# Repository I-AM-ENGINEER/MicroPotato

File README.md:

# MicroPotato
Old allwinner v3s devboard created just for fun

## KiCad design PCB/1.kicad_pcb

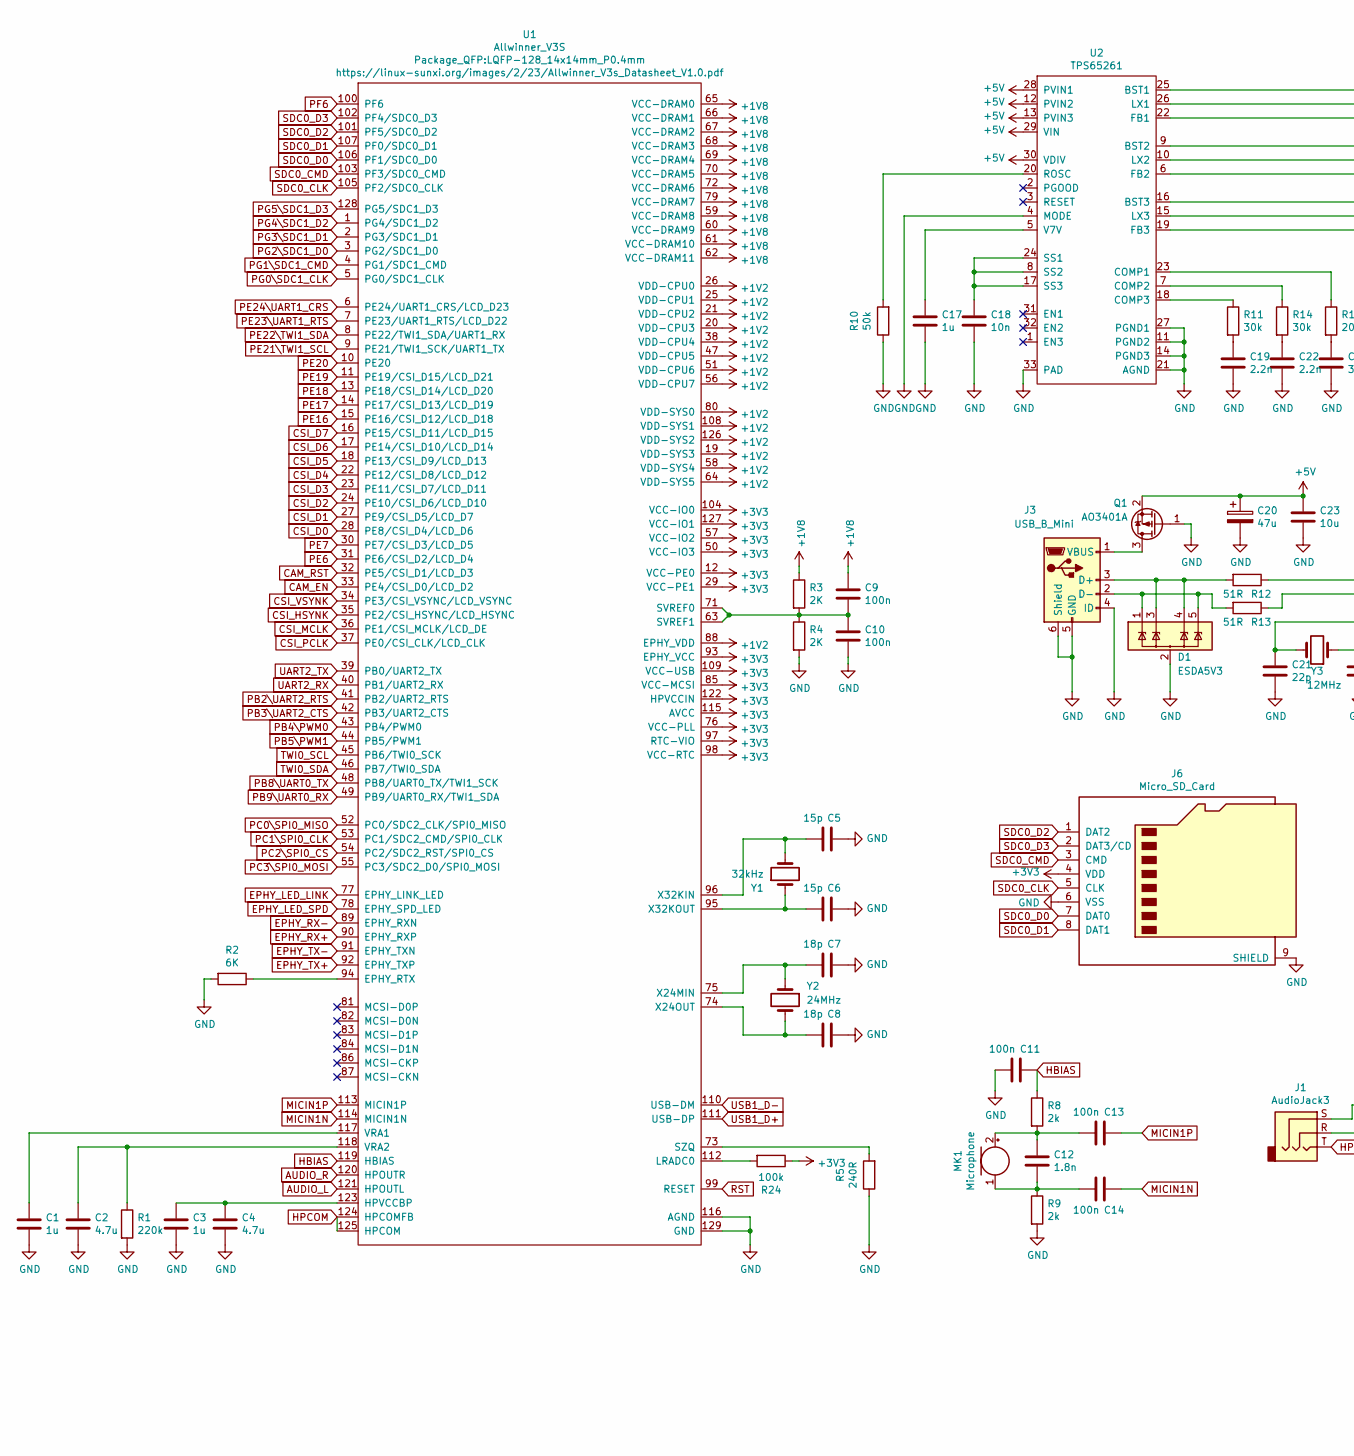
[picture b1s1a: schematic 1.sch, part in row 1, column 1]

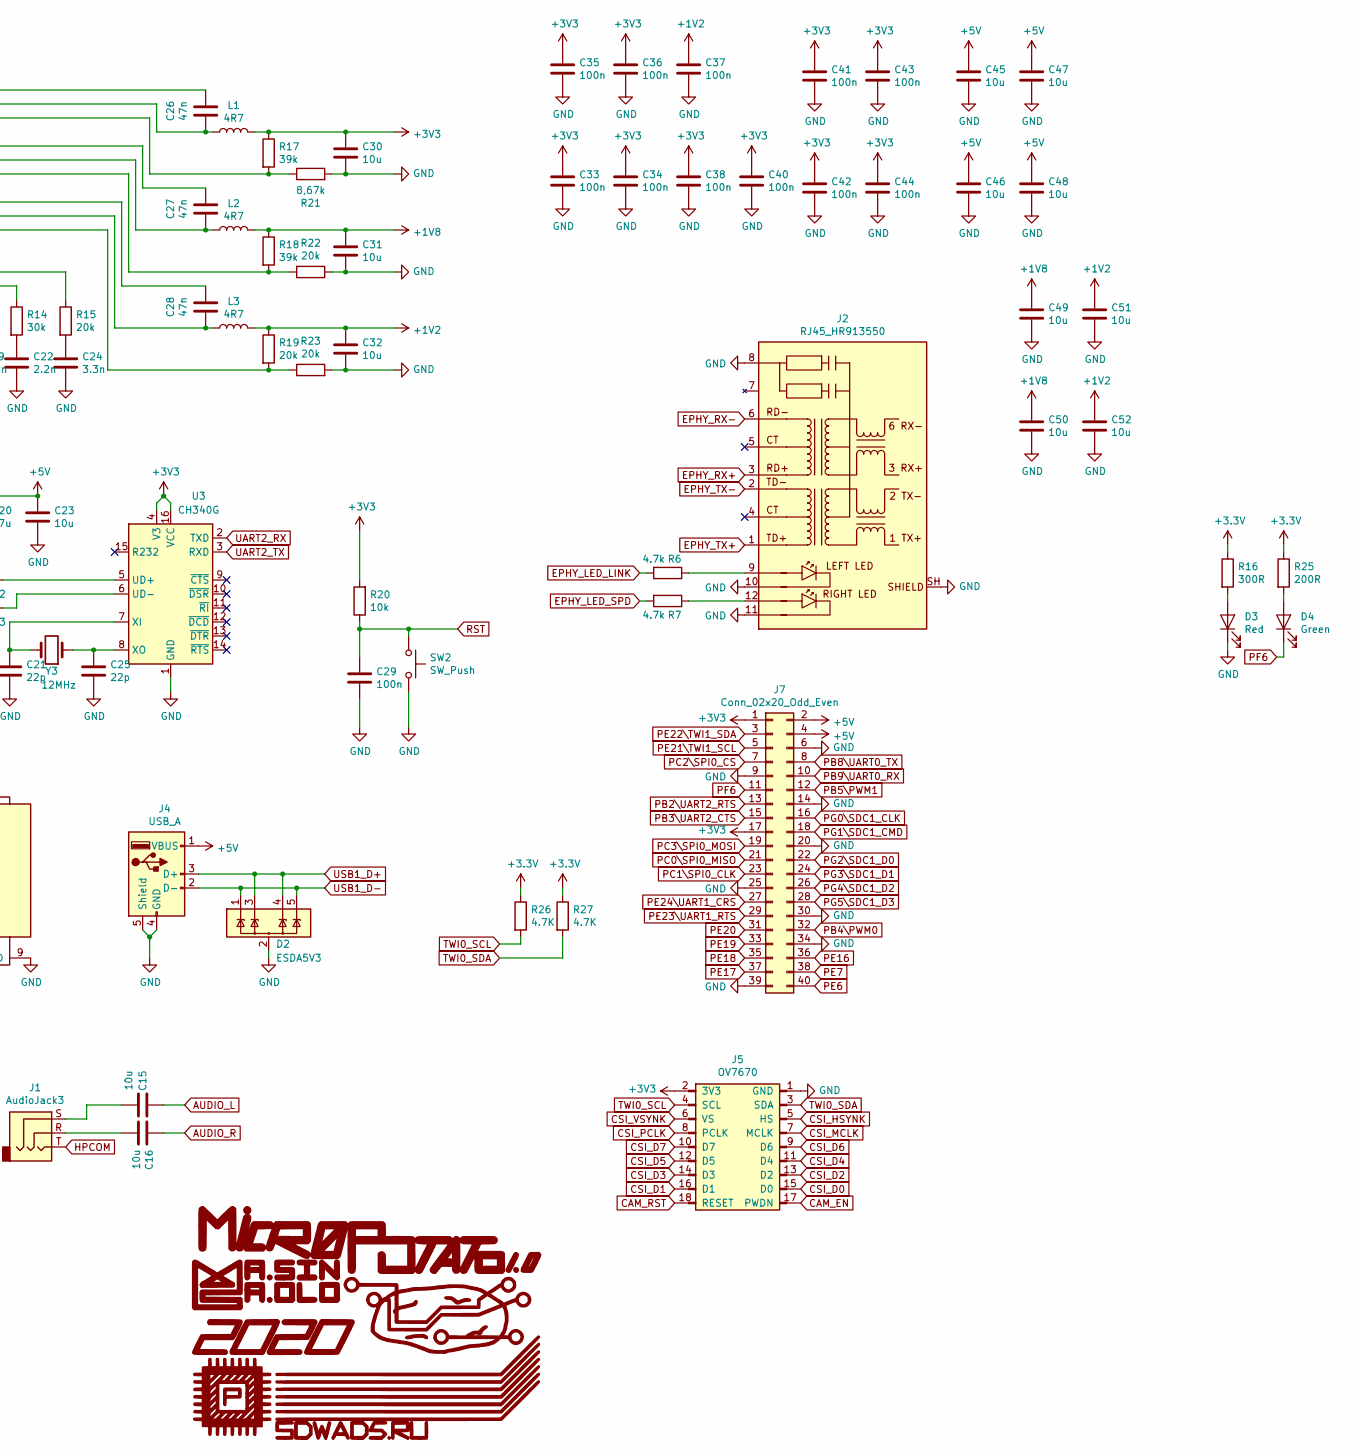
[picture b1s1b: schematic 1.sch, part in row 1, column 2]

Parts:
C1, C3, C17: 1u; C_0603_1608Metric
C2, C4: 4.7u; C_0603_1608Metric
C5, C6: 15p; C_0603_1608Metric
C7, C8: 18p; C_0603_1608Metric
C9, C10, C11, C13, C14, C29, C33, C34, C35, C36, C37, C38, C40, C41, C42, C43: 100n; C_0603_1608Metric
C12: 1.8n; C_0603_1608Metric
C15, C16, C23, C30, C31, C32, C45, C46, C47, C49, C51: 10u; C_0603_1608Metric
C18: 10n; C_0603_1608Metric
C19, C22: 2.2n; C_0603_1608Metric
C20: 47u; CP_Elec_6.3x5.7
C21, C25: 22p; C_0603_1608Metric
C24: 3.3n; C_0603_1608Metric
C26, C27, C28: 47n; C_0603_1608Metric
C44: 100n; C_0603_1608Metric_Pad1.05x0.95mm_HandSolder
C48, C50, C52: 10u; C_0603_1608Metric_Pad1.05x0.95mm_HandSolder
D1, D2: ESDA5V3; SOT-23-5
D3: Red; LED_0603_1608Metric
D4: Green; LED_0603_1608Metric
J1: AudioJack3; Jack_3.5mm_Switronic_ST-005-G_horizontal
J2: RJ45_HR913550; RJ45_Hanrun_HR911105A
J3: USB_B_Mini; USB_Mini-B_Lumberg_2486_01_Horizontal
J4: USB_A; USB_A_C42421
J5: OV7670; PinSocket_2x09_P2.54mm_Vertical
J6: Micro_SD_Card; microSD_TF115K
J7: Conn_02x20_Odd_Even; PinHeader_2x20_P2.54mm_Vertical
L1, L2, L3: 4R7; L_Bourns-SRN4018
MK1: Microphone; MIC_10mm
Q1: AO3401A; SOT-23
R1: 220k; R_0603_1608Metric
R2: 6K; R_0603_1608Metric
R3, R4: 2K; R_0603_1608Metric
R5: 240R; R_0603_1608Metric
R6, R7: 4.7k; R_0603_1608Metric
R8, R9: 2k; R_0603_1608Metric
R10: 50k; R_0603_1608Metric
R11, R14: 30k; R_0603_1608Metric
R12, R13: 51R; R_0603_1608Metric
R15, R19, R22, R23: 20k; R_0603_1608Metric
R16: 300R; R_0603_1608Metric
R17, R18: 39k; R_0603_1608Metric
R20: 10k; R_0603_1608Metric
R21: 8,67k; R_0603_1608Metric
R24: 100k; R_0603_1608Metric
R25: 200R; R_0603_1608Metric
R26, R27: 4.7K; R_0603_1608Metric
SW2: SW_Push; SW_SPST_B3SL-1022P
U1: Allwinner_V3S; LQFP-128_14x14mm_P0.4mm
U2: TPS65261; QFN-32-1EP_5x5mm_P0.5mm_EP3.45x3.45mm
U3: CH340G; SOIC-16_3.9x9.9mm_P1.27mm
Y1: 32kHz; Crystal_C38-LF_D3.0mm_L8.0mm_Horizontal_1EP_style1
Y2: 24MHz; Crystal_SMD_5032-2Pin_5.0x3.2mm_HandSoldering
Y3: 12MHz; Crystal_SMD_5032-2Pin_5.0x3.2mm_HandSoldering

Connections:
+1V2: C32.1, C37.1, C51.1, C52.1, L3.2, R19.1, U1.19 (VDD-SYS3), U1.20 (VDD-CPU3), U1.21 (VDD-CPU2), U1.25 (VDD-CPU1), U1.26 (VDD-CPU0), U1.38 (VDD-CPU4), U1.47 (VDD-CPU5), U1.51 (VDD-CPU6), U1.56 (VDD-CPU7), U1.58 (VDD-SYS4), U1.64 (VDD-SYS5), U1.80 (VDD-SYS0), U1.88 (EPHY_VDD), U1.108 (VDD-SYS1), U1.126 (VDD-SYS2)
+1V8: C9.1, C31.1, C49.1, C50.1, L2.2, R3.1, R18.1, U1.59 (VCC-DRAM8), U1.60 (VCC-DRAM9), U1.61 (VCC-DRAM10), U1.62 (VCC-DRAM11), U1.65 (VCC-DRAM0), U1.66 (VCC-DRAM1), U1.67 (VCC-DRAM2), U1.68 (VCC-DRAM3), U1.69 (VCC-DRAM4), U1.70 (VCC-DRAM5), U1.72 (VCC-DRAM6), U1.79 (VCC-DRAM7)
+5V: C20.1, C23.1, C45.1, C46.1, C47.1, C48.1, J4.1 (VBUS), J7.2, J7.4, Q1.2 (S), U2.12 (PVIN2), U2.13 (PVIN3), U2.28 (PVIN1), U2.29 (VIN), U2.30 (VDIV)
AUDIO_L: C15.1, U1.121 (HPOUTL)
AUDIO_R: C16.1, U1.120 (HPOUTR)
CAM_EN: J5.17 (PWDN), U1.33 (PE4/CSI_D0/LCD_D2)
CAM_RST: J5.18 (RESET), U1.32 (PE5/CSI_D1/LCD_D3)
CSI_D0: J5.15 (D0), U1.28 (PE8/CSI_D4/LCD_D6)
CSI_D1: J5.16 (D1), U1.27 (PE9/CSI_D5/LCD_D7)
CSI_D2: J5.13 (D2), U1.24 (PE10/CSI_D6/LCD_D10)
CSI_D3: J5.14 (D3), U1.23 (PE11/CSI_D7/LCD_D11)
CSI_D4: J5.11 (D4), U1.22 (PE12/CSI_D8/LCD_D12)
CSI_D5: J5.12 (D5), U1.18 (PE13/CSI_D9/LCD_D13)
CSI_D6: J5.9 (D6), U1.17 (PE14/CSI_D10/LCD_D14)
CSI_D7: J5.10 (D7), U1.16 (PE15/CSI_D11/LCD_D15)
CSI_HSYNK: J5.5 (HS), U1.35 (PE2/CSI_HSYNC/LCD_HSYNC)
CSI_MCLK: J5.7 (MCLK), U1.36 (PE1/CSI_MCLK/LCD_DE)
CSI_PCLK: J5.8 (PCLK), U1.37 (PE0/CSI_CLK/LCD_CLK)
CSI_VSYNK: J5.6 (VS), U1.34 (PE3/CSI_VSYNC/LCD_VSYNC)
EPHY_LED_LINK: R6.2, U1.77 (EPHY_LINK_LED)
EPHY_LED_SPD: R7.2, U1.78 (EPHY_SPD_LED)
EPHY_RX+: J2.3 (RD+), U1.90 (EPHY_RXP)
EPHY_RX-: J2.6 (RD-), U1.89 (EPHY_RXN)
EPHY_TX+: J2.1 (TD+), U1.92 (EPHY_TXP)
EPHY_TX-: J2.2 (TD-), U1.91 (EPHY_TXN)
GND: C1.2, C2.2, C3.2, C4.2, C5.1, C6.1, C7.1, C8.1, C10.2, C11.2, C17.2, C18.2, C19.2, C20.2, C21.1, C22.2, C23.2, C24.2, C25.2, C29.2, C30.2, C31.2, C32.2, C33.2, C34.2, C35.2, C36.2, C37.2, C38.2, C40.2, C41.2, C42.2, C43.2, C44.2, C45.2, C46.2, C47.2, C48.2, C49.2, C50.2, C51.2, C52.2, D1.2 (GND), D2.2 (GND), D3.1 (K), J2.8, J2.10 (LLED-), J2.11 (RLED-), J2.SH (SHIELD), J3.4 (ID), J3.5 (GND), J3.6 (Shield), J4.4 (GND), J4.5 (Shield), J5.1 (GND), J6.6 (VSS), J6.9 (SHIELD), J7.6, J7.9, J7.14, J7.20, J7.25, J7.30, J7.34, J7.39, Q1.1 (G), R1.2, R2.2, R4.2, R5.1, R9.2, R10.1, R21.2, R22.1, R23.2, SW2.2, U1.116 (AGND), U1.129 (GND), U2.4 (MODE), U2.11 (PGND2), U2.14 (PGND3), U2.21 (AGND), U2.27 (PGND1), U2.33 (PAD), U3.1 (GND)
HBIAS: C11.1, R8.1, U1.119 (HBIAS)
HPCOM: J1.T, U1.124 (HPCOMFB), U1.125 (HPCOM)
MICIN1N: C14.1, U1.114 (MICIN1N)
MICIN1P: C13.1, U1.113 (MICIN1P)
unnamed: C1.1, U1.117 (VRA1)
unnamed: C2.1, R1.1, U1.118 (VRA2)
unnamed: C3.1, C4.1, U1.123 (HPVCCBP)
unnamed: C5.2, U1.96 (X32KIN), Y1.2
unnamed: C6.2, U1.95 (X32KOUT), Y1.1
unnamed: C7.2, U1.75 (X24MIN), Y2.1
unnamed: C8.2, U1.74 (X24OUT), Y2.2
unnamed: C9.2, C10.1, R3.2, R4.1, U1.63 (SVREF1), U1.71 (SVREF0)
unnamed: C12.1, C13.2, MK1.2 (+), R8.2
unnamed: C12.2, C14.2, MK1.1 (-), R9.1
unnamed: C15.2, J1.S
unnamed: C16.2, J1.R
unnamed: C17.1, U2.5 (V7V)
unnamed: C18.1, U2.8 (SS2), U2.17 (SS3), U2.24 (SS1)
unnamed: C19.1, R11.2
unnamed: C21.2, U3.7 (XI), Y3.2
unnamed: C22.1, R14.2
unnamed: C24.1, R15.2
unnamed: C25.1, U3.8 (XO), Y3.1
unnamed: C26.1, U2.25 (BST1)
unnamed: C26.2, L1.1, U2.26 (LX1)
unnamed: C27.1, U2.9 (BST2)
unnamed: C27.2, L2.1, U2.10 (LX2)
unnamed: C28.1, U2.16 (BST3)
unnamed: C28.2, L3.1, U2.15 (LX3)
unnamed: D1.1 (IO1), D1.5 (IO5), J3.2 (D-), R13.2
unnamed: D1.3 (IO2), D1.4 (IO4), J3.3 (D+), R12.2
unnamed: D3.2 (A), R16.2
unnamed: D4.2 (A), R25.2
unnamed: J2.9 (LLED+), R6.1
unnamed: J2.12 (RLED+), R7.1
unnamed: J3.1 (VBUS), Q1.3 (D)
unnamed: R2.1, U1.94 (EPHY_RTX)
unnamed: R5.2, U1.73 (SZQ)
unnamed: R10.2, U2.20 (ROSC)
unnamed: R11.1, U2.18 (COMP3)
unnamed: R12.1, U3.5 (UD+)
unnamed: R13.1, U3.6 (UD-)
unnamed: R14.1, U2.7 (COMP2)
unnamed: R15.1, U2.23 (COMP1)
unnamed: R17.2, R21.1, U2.22 (FB1)
unnamed: R18.2, R22.2, U2.6 (FB2)
unnamed: R19.2, R23.1, U2.19 (FB3)
unnamed: R24.2, U1.112 (LRADC0)
PB2\UART2_RTS: J7.13, U1.41 (PB2/UART2_RTS)
PB3\UART2_CTS: J7.15, U1.42 (PB3/UART2_CTS)
PB4\PWM0: J7.32, U1.43 (PB4/PWM0)
PB5\PWM1: J7.12, U1.44 (PB5/PWM1)
PB8\UART0_TX: J7.8, U1.48 (PB8/UART0_TX/TWI1_SCK)
PB9\UART0_RX: J7.10, U1.49 (PB9/UART0_RX/TWI1_SDA)
PC0\SPI0_MISO: J7.21, U1.52 (PC0/SDC2_CLK/SPI0_MISO)
PC1\SPI0_CLK: J7.23, U1.53 (PC1/SDC2_CMD/SPI0_CLK)
PC2\SPI0_CS: J7.7, U1.54 (PC2/SDC2_RST/SPI0_CS)
PC3\SPI0_MOSI: J7.19, U1.55 (PC3/SDC2_D0/SPI0_MOSI)
PE6: J7.40, U1.31 (PE6/CSI_D2/LCD_D4)
PE7: J7.38, U1.30 (PE7/CSI_D3/LCD_D5)
PE16: J7.36, U1.15 (PE16/CSI_D12/LCD_D18)
PE17: J7.37, U1.14 (PE17/CSI_D13/LCD_D19)
PE18: J7.35, U1.13 (PE18/CSI_D14/LCD_D20)
PE19: J7.33, U1.11 (PE19/CSI_D15/LCD_D21)
PE20: J7.31, U1.10 (PE20)
PE21\TWI1_SCL: J7.5, U1.9 (PE21/TWI1_SCK/UART1_TX)
PE22\TWI1_SDA: J7.3, U1.8 (PE22/TWI1_SDA/UART1_RX)
PE23\UART1_RTS: J7.29, U1.7 (PE23/UART1_RTS/LCD_D22)
PE24\UART1_CRS: J7.27, U1.6 (PE24/UART1_CRS/LCD_D23)
PF6: D4.1 (K), J7.11, U1.100 (PF6)
PG0\SDC1_CLK: J7.16, U1.5 (PG0/SDC1_CLK)
PG1\SDC1_CMD: J7.18, U1.4 (PG1/SDC1_CMD)
PG2\SDC1_D0: J7.22, U1.3 (PG2/SDC1_D0)
PG3\SDC1_D1: J7.24, U1.2 (PG3/SDC1_D1)
PG4\SDC1_D2: J7.26, U1.1 (PG4/SDC1_D2)
PG5\SDC1_D3: J7.28, U1.128 (PG5/SDC1_D3)
RST: C29.1, R20.1, SW2.1, U1.99 (RESET)
SDC0_CLK: J6.5 (CLK), U1.105 (PF2/SDC0_CLK)
SDC0_CMD: J6.3 (CMD), U1.103 (PF3/SDC0_CMD)
SDC0_D0: J6.7 (DAT0), U1.106 (PF1/SDC0_D0)
SDC0_D1: J6.8 (DAT1), U1.107 (PF0/SDC0_D1)
SDC0_D2: J6.1 (DAT2), U1.101 (PF5/SDC0_D2)
SDC0_D3: J6.2 (DAT3/CD), U1.102 (PF4/SDC0_D3)
TWI0_SCL: J5.4 (SCL), R26.2, U1.45 (PB6/TWI0_SCK)
TWI0_SDA: J5.3 (SDA), R27.2, U1.46 (PB7/TWI0_SDA)
UART2_RX: U1.40 (PB1/UART2_RX), U3.2 (TXD)
UART2_TX: U1.39 (PB0/UART2_TX), U3.3 (RXD)
USB1_D+: D2.3 (IO2), D2.4 (IO4), J4.3 (D+), U1.111 (USB-DP)
USB1_D-: D2.1 (IO1), D2.5 (IO5), J4.2 (D-), U1.110 (USB-DM)

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
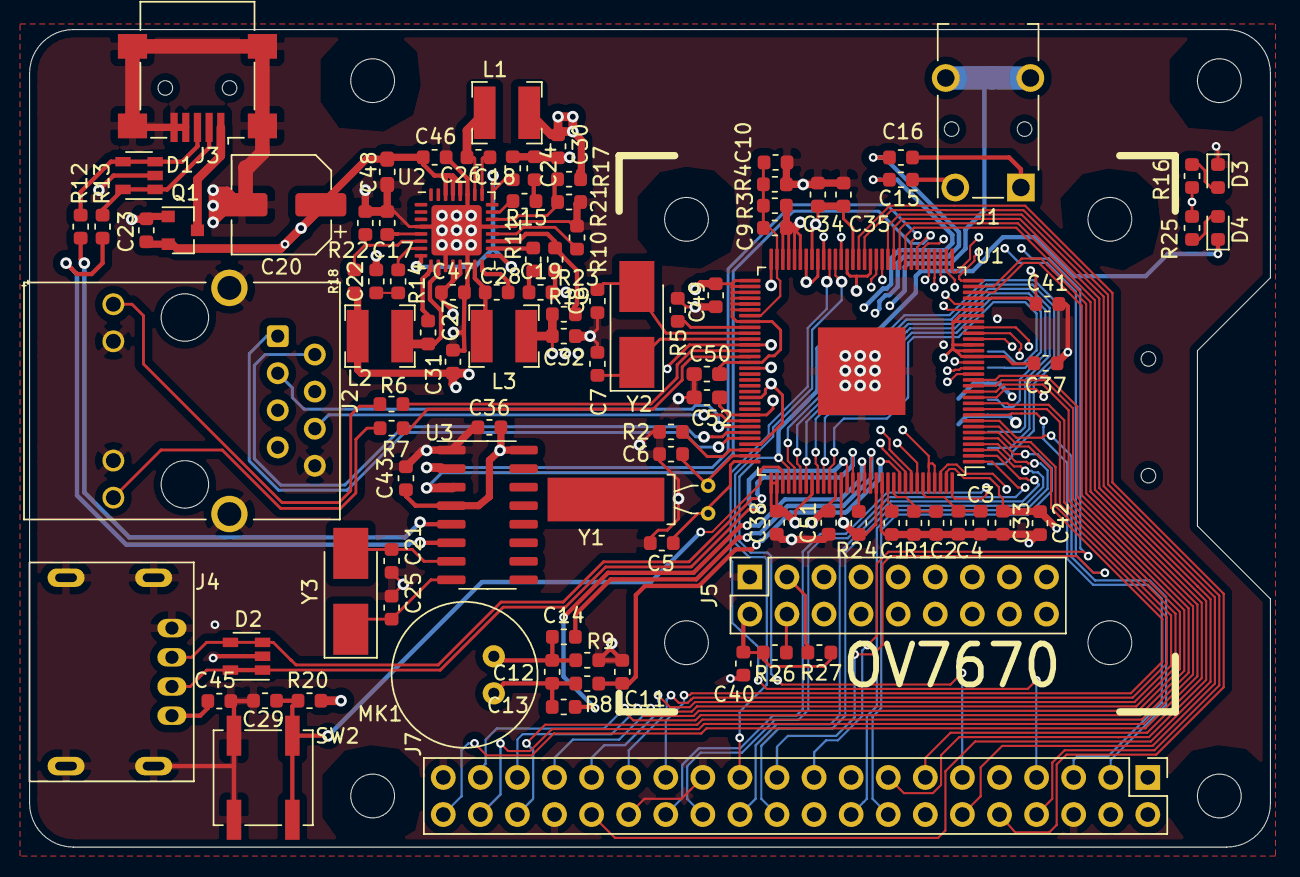
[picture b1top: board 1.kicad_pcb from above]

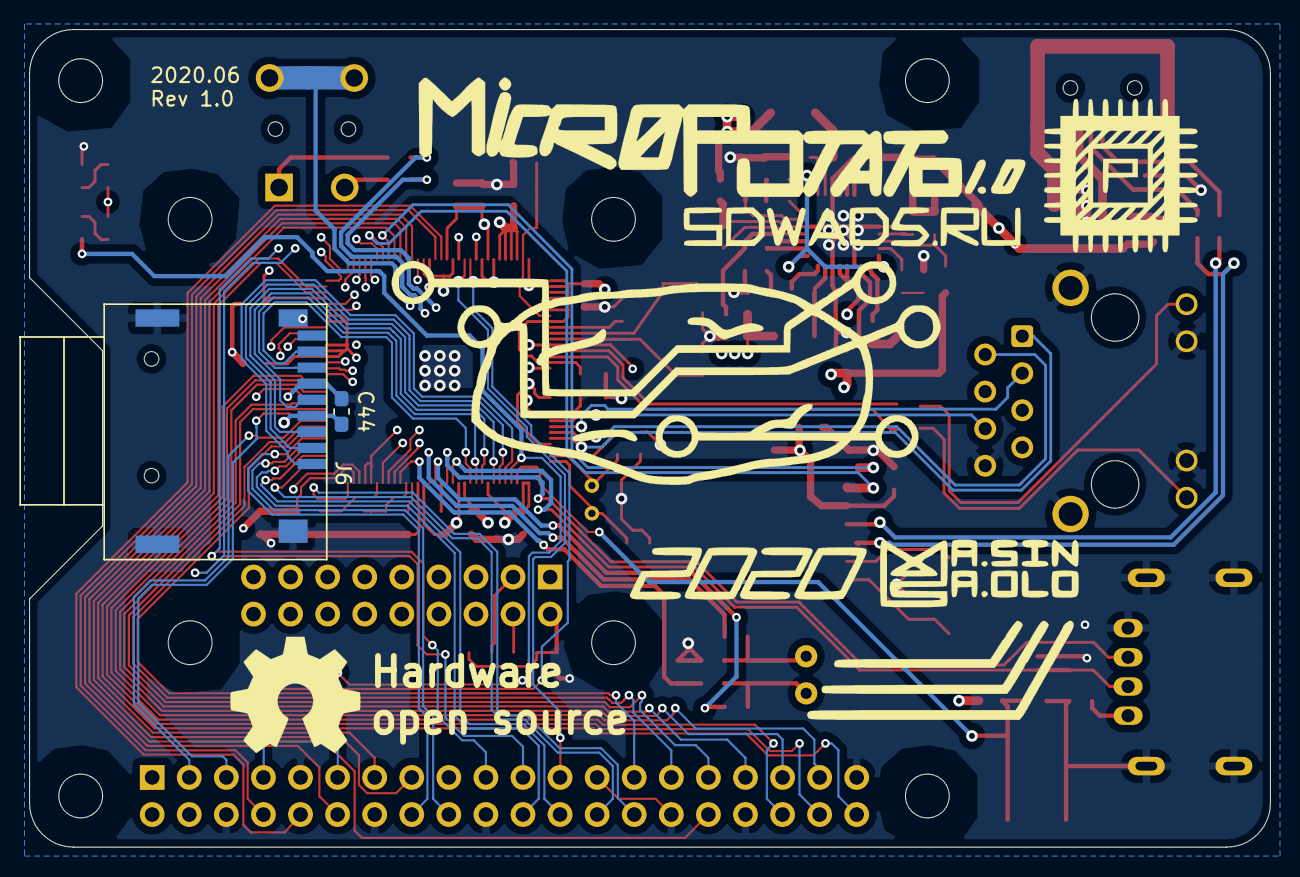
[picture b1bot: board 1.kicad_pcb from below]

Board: 4 copper layers, 85.0 x 56.0 mm, 101 parts (2 on the bottom side), 116 nets.
